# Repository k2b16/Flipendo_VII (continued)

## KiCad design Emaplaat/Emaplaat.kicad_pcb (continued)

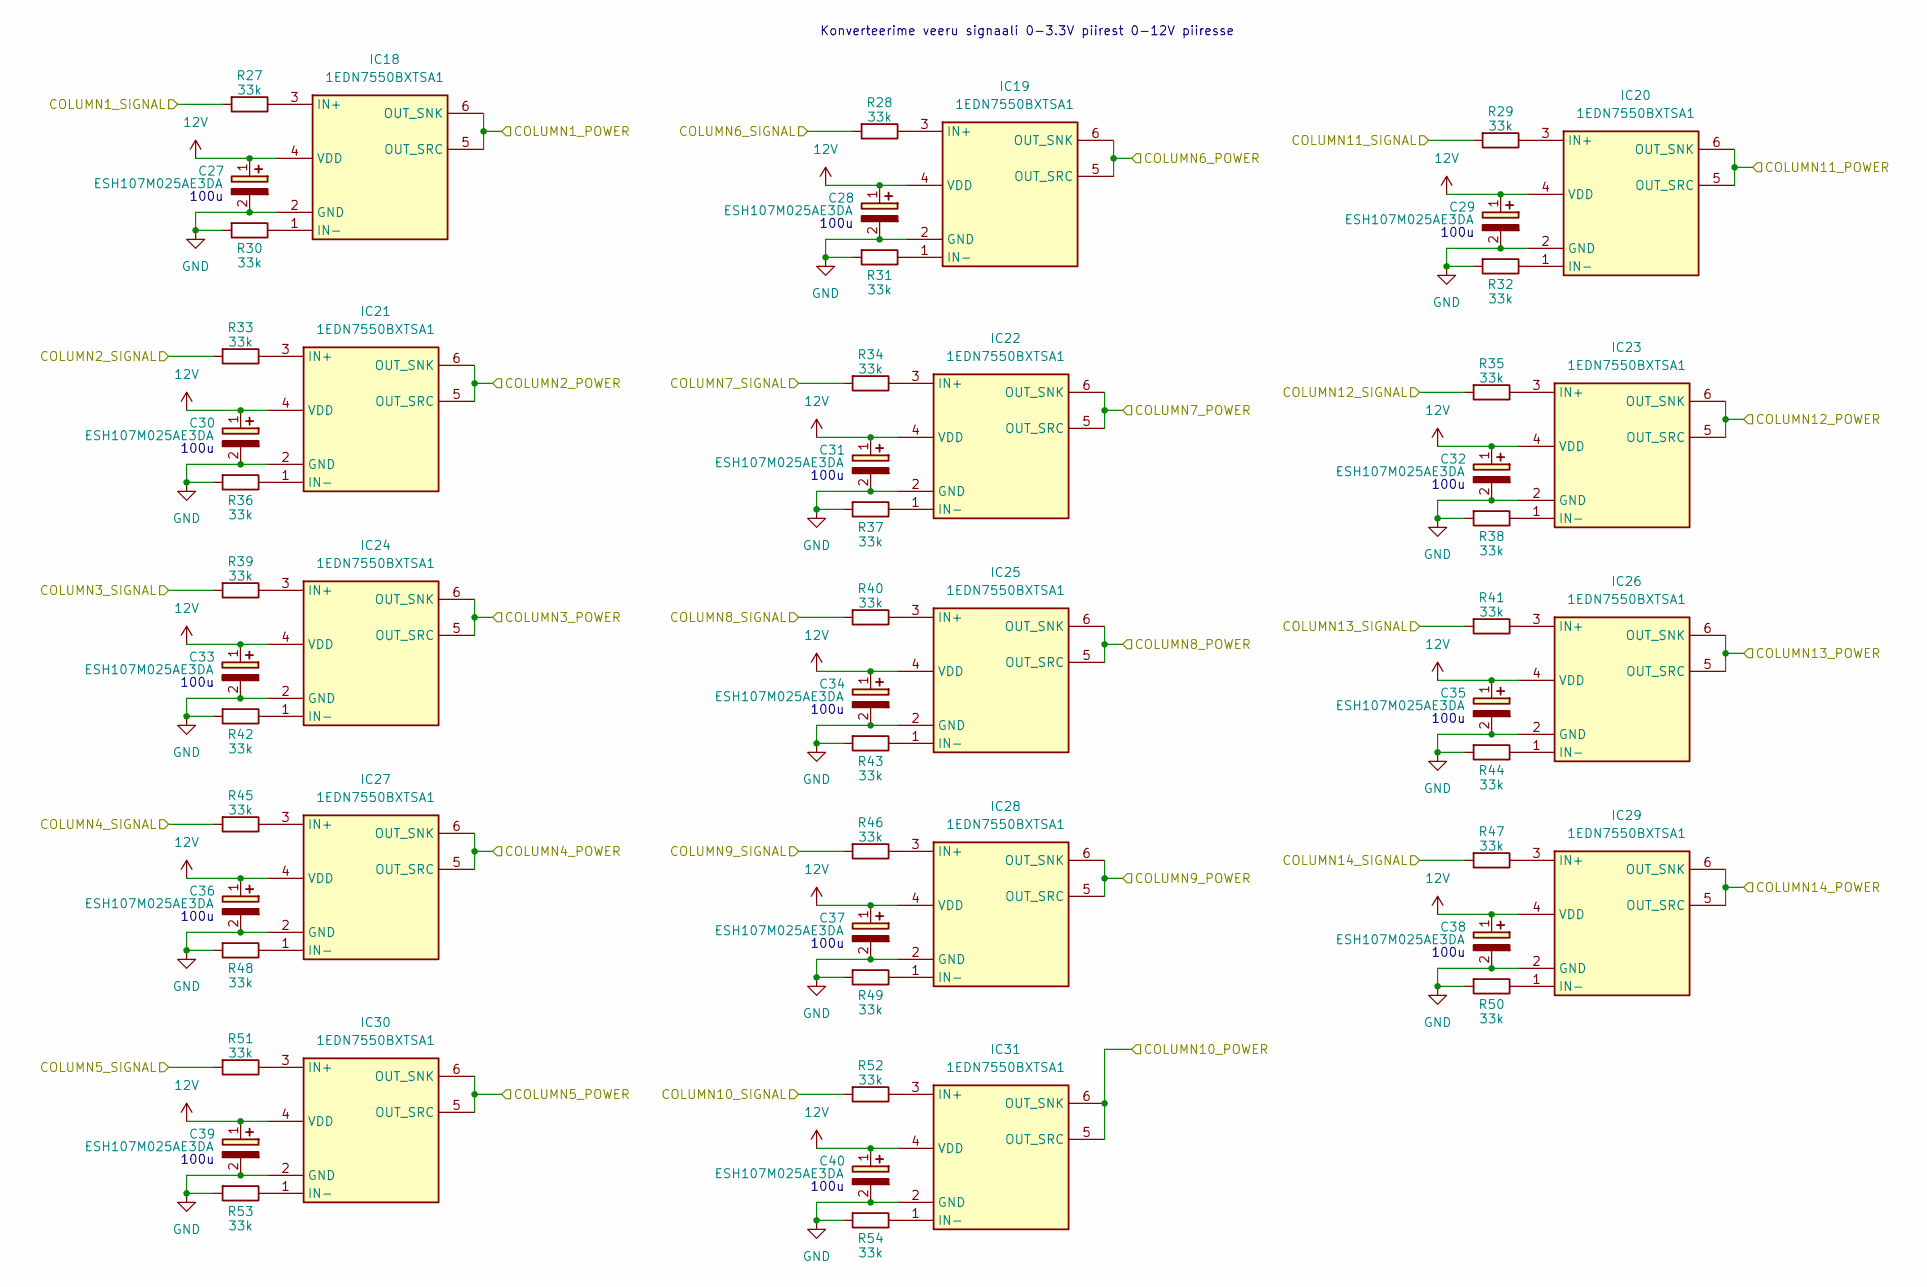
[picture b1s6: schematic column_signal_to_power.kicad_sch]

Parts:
C27, C28, C29, C30, C31, C32, C33, C34, C35, C36, C37, C38, C39, C40: ESH107M025AE3DA; CAPPRD250W50D630H1250; Mouser Part Number 80-ESH107M025AE3DA
IC18, IC19, IC20, IC21, IC22, IC23, IC24, IC25, IC26, IC27, IC28, IC29, IC30, IC31: 1EDN7550BXTSA1; SOT95P280X145-6N; Mouser Part Number 726-1EDN7550BXTSA1
R27, R28, R29, R30, R31, R32, R33, R34, R35, R36, R37, R38, R39, R40, R41, R42, R43, R44, R45, R46, R47, R48, R49, R50, R51, R52, R53, R54: 33k; R_0603_1608Metric_Pad0.98x0.95mm_HandSolder

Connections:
12V: C27.1 (+), C28.1 (+), C29.1 (+), C30.1 (+), C31.1 (+), C32.1 (+), C33.1 (+), C34.1 (+), C35.1 (+), C36.1 (+), C37.1 (+), C38.1 (+), C39.1 (+), C40.1 (+), IC18.4 (VDD), IC19.4 (VDD), IC20.4 (VDD), IC21.4 (VDD), IC22.4 (VDD), IC23.4 (VDD), IC24.4 (VDD), IC25.4 (VDD), IC26.4 (VDD), IC27.4 (VDD), IC28.4 (VDD), IC29.4 (VDD), IC30.4 (VDD), IC31.4 (VDD); also elsewhere on the board
/COLUMN1: R27.2; also elsewhere on the board
/COLUMN2: R33.2; also elsewhere on the board
/COLUMN3: R39.2; also elsewhere on the board
/COLUMN4: R45.2; also elsewhere on the board
/COLUMN5: R51.2; also elsewhere on the board
/COLUMN6: R28.2; also elsewhere on the board
/COLUMN7: R34.2; also elsewhere on the board
/COLUMN8: R40.2; also elsewhere on the board
/COLUMN9: R46.2; also elsewhere on the board
/COLUMN10: R52.2; also elsewhere on the board
/COLUMN11: R29.2; also elsewhere on the board
/COLUMN12: R35.2; also elsewhere on the board
/COLUMN13: R41.2; also elsewhere on the board
/COLUMN14: R47.2; also elsewhere on the board
/ekraan/COLUMN1_POWER: IC18.5 (OUT_SRC), IC18.6 (OUT_SNK); also elsewhere on the board
/ekraan/COLUMN2_POWER: IC21.5 (OUT_SRC), IC21.6 (OUT_SNK); also elsewhere on the board
/ekraan/COLUMN3_POWER: IC24.5 (OUT_SRC), IC24.6 (OUT_SNK); also elsewhere on the board
/ekraan/COLUMN4_POWER: IC27.5 (OUT_SRC), IC27.6 (OUT_SNK); also elsewhere on the board
/ekraan/COLUMN5_POWER: IC30.5 (OUT_SRC), IC30.6 (OUT_SNK); also elsewhere on the board
/ekraan/COLUMN6_POWER: IC19.5 (OUT_SRC), IC19.6 (OUT_SNK); also elsewhere on the board
/ekraan/COLUMN7_POWER: IC22.5 (OUT_SRC), IC22.6 (OUT_SNK); also elsewhere on the board
/ekraan/COLUMN8_POWER: IC25.5 (OUT_SRC), IC25.6 (OUT_SNK); also elsewhere on the board
/ekraan/COLUMN9_POWER: IC28.5 (OUT_SRC), IC28.6 (OUT_SNK); also elsewhere on the board
/ekraan/COLUMN10_POWER: IC31.5 (OUT_SRC), IC31.6 (OUT_SNK); also elsewhere on the board
/ekraan/COLUMN11_POWER: IC20.5 (OUT_SRC), IC20.6 (OUT_SNK); also elsewhere on the board
/ekraan/COLUMN12_POWER: IC23.5 (OUT_SRC), IC23.6 (OUT_SNK); also elsewhere on the board
/ekraan/COLUMN13_POWER: IC26.5 (OUT_SRC), IC26.6 (OUT_SNK); also elsewhere on the board
/ekraan/COLUMN14_POWER: IC29.5 (OUT_SRC), IC29.6 (OUT_SNK); also elsewhere on the board
GND: C27.2 (-), C28.2 (-), C29.2 (-), C30.2 (-), C31.2 (-), C32.2 (-), C33.2 (-), C34.2 (-), C35.2 (-), C36.2 (-), C37.2 (-), C38.2 (-), C39.2 (-), C40.2 (-), IC18.2 (GND), IC19.2 (GND), IC20.2 (GND), IC21.2 (GND), IC22.2 (GND), IC23.2 (GND), IC24.2 (GND), IC25.2 (GND), IC26.2 (GND), IC27.2 (GND), IC28.2 (GND), IC29.2 (GND), IC30.2 (GND), IC31.2 (GND), R30.2, R31.2, R32.2, R36.2, R37.2, R38.2, R42.2, R43.2, R44.2, R48.2, R49.2, R50.2, R53.2, R54.2; also elsewhere on the board
unnamed: IC18.3 (IN+), R27.1
unnamed: IC18.1 (IN-), R30.1
unnamed: IC19.3 (IN+), R28.1
unnamed: IC19.1 (IN-), R31.1
unnamed: IC20.3 (IN+), R29.1
unnamed: IC20.1 (IN-), R32.1
unnamed: IC21.3 (IN+), R33.1
unnamed: IC21.1 (IN-), R36.1
unnamed: IC22.3 (IN+), R34.1
unnamed: IC22.1 (IN-), R37.1
unnamed: IC23.3 (IN+), R35.1
unnamed: IC23.1 (IN-), R38.1
unnamed: IC24.3 (IN+), R39.1
unnamed: IC24.1 (IN-), R42.1
unnamed: IC25.3 (IN+), R40.1
unnamed: IC25.1 (IN-), R43.1
unnamed: IC26.3 (IN+), R41.1
unnamed: IC26.1 (IN-), R44.1
unnamed: IC27.3 (IN+), R45.1
unnamed: IC27.1 (IN-), R48.1
unnamed: IC28.3 (IN+), R46.1
unnamed: IC28.1 (IN-), R49.1
unnamed: IC29.3 (IN+), R47.1
unnamed: IC29.1 (IN-), R50.1
unnamed: IC30.3 (IN+), R51.1
unnamed: IC30.1 (IN-), R53.1
unnamed: IC31.3 (IN+), R52.1
unnamed: IC31.1 (IN-), R54.1

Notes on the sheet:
100u
Konverteerime veeru signaali 0-3.3V piirest 0-12V piiresse

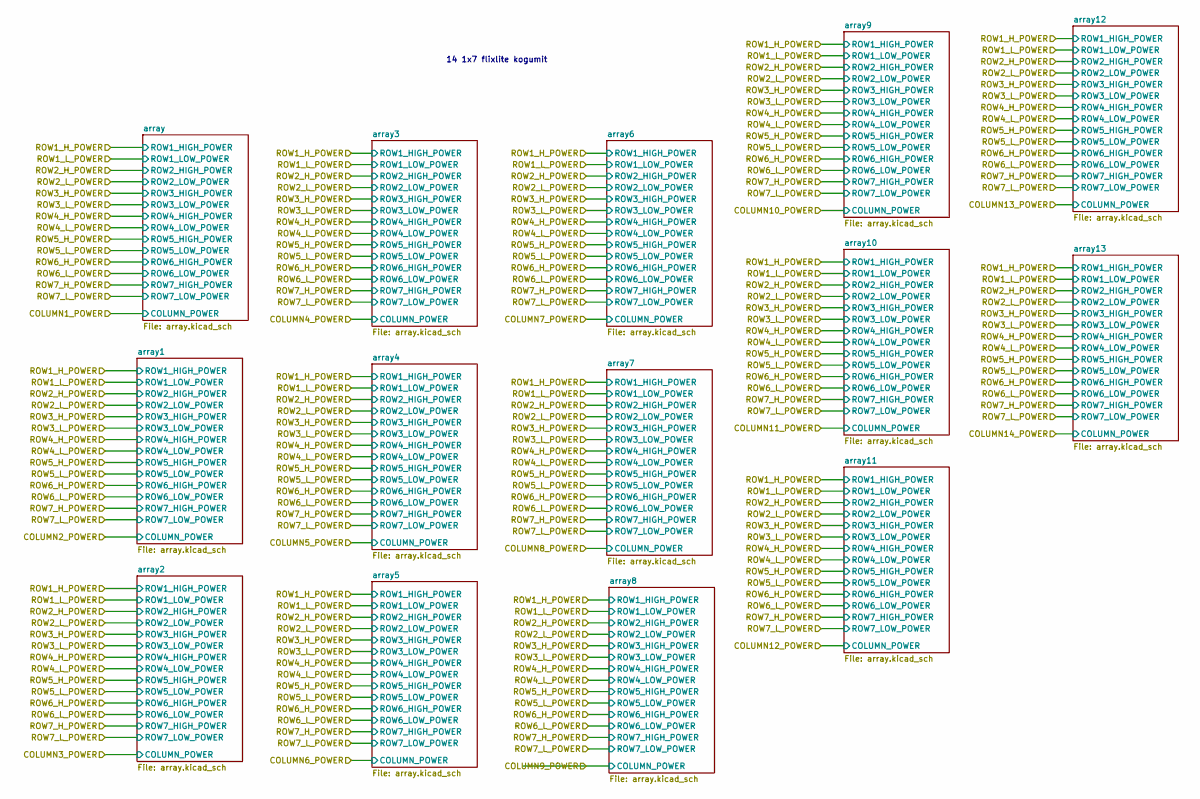
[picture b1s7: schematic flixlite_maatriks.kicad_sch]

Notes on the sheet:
14 1x7 flixlite kogumit

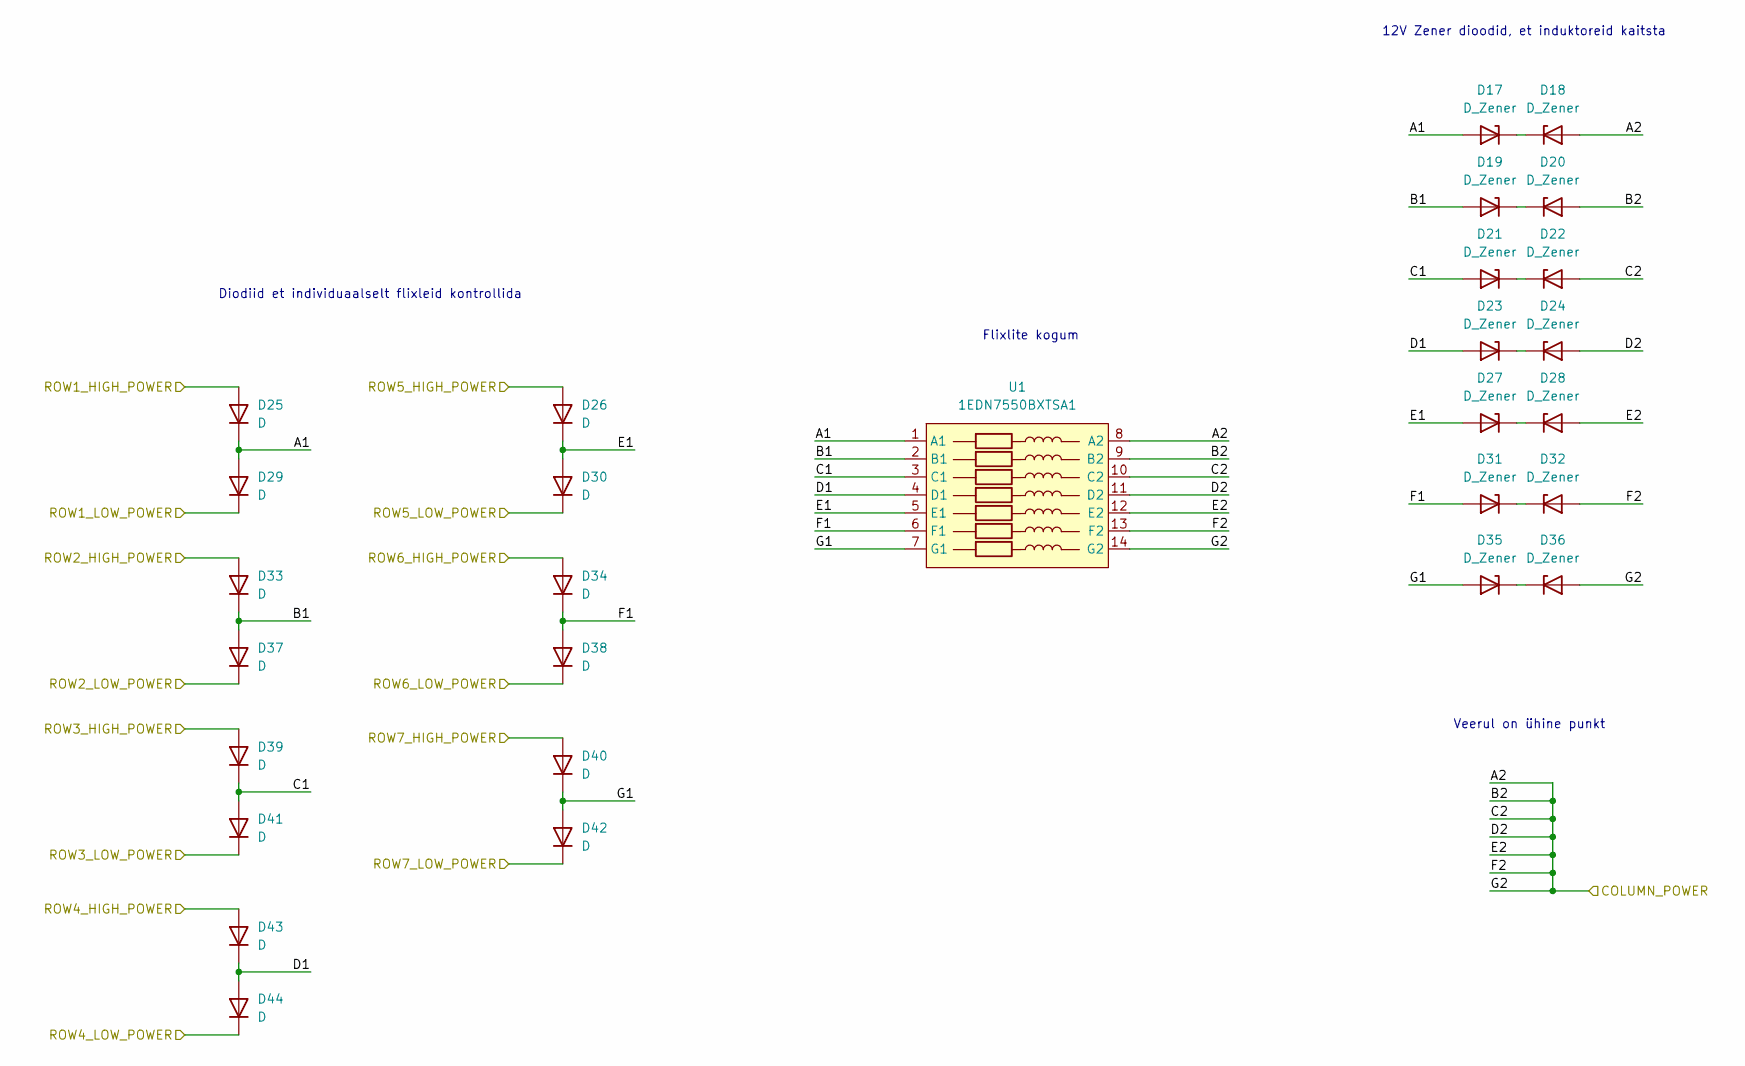
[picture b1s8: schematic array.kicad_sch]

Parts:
D17, D18, D19, D20, D21, D22, D23, D24, D27, D28, D31, D32, D35, D36: D_Zener; DO-214AC-2
D25, D26, D29, D30, D33, D34, D37, D38, D39, D40, D41, D42, D43, D44: D; SOD-123FL
U1: 1EDN7550BXTSA1; 7_flip_dots

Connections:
/ekraan/COLUMN1_POWER: D18.2 (A), D20.2 (A), D22.2 (A), D24.2 (A), D28.2 (A), D32.2 (A), D36.2 (A), U1.8 (A2), U1.9 (B2), U1.10 (C2), U1.11 (D2), U1.12 (E2), U1.13 (F2), U1.14 (G2); also elsewhere on the board
/ekraan/Flixlite_maatriks/array/A1: D17.2 (A), D25.1 (K), D29.2 (A), U1.1 (A1)
/ekraan/Flixlite_maatriks/array/B1: D19.2 (A), D33.1 (K), D37.2 (A), U1.2 (B1)
/ekraan/Flixlite_maatriks/array/C1: D21.2 (A), D39.1 (K), D41.2 (A), U1.3 (C1)
/ekraan/Flixlite_maatriks/array/D1: D23.2 (A), D43.1 (K), D44.2 (A), U1.4 (D1)
/ekraan/Flixlite_maatriks/array/E1: D26.1 (K), D27.2 (A), D30.2 (A), U1.5 (E1)
/ekraan/Flixlite_maatriks/array/F1: D31.2 (A), D34.1 (K), D38.2 (A), U1.6 (F1)
/ekraan/Flixlite_maatriks/array/G1: D35.2 (A), D40.1 (K), D42.2 (A), U1.7 (G1)
/ekraan/ROW1_H_POWER: D25.2 (A); also elsewhere on the board
/ekraan/ROW1_L_POWER: D29.1 (K); also elsewhere on the board
/ekraan/ROW2_H_POWER: D33.2 (A); also elsewhere on the board
/ekraan/ROW2_L_POWER: D37.1 (K); also elsewhere on the board
/ekraan/ROW3_H_POWER: D39.2 (A); also elsewhere on the board
/ekraan/ROW3_L_POWER: D41.1 (K); also elsewhere on the board
/ekraan/ROW4_H_POWER: D43.2 (A); also elsewhere on the board
/ekraan/ROW4_L_POWER: D44.1 (K); also elsewhere on the board
/ekraan/ROW5_H_POWER: D26.2 (A); also elsewhere on the board
/ekraan/ROW5_L_POWER: D30.1 (K); also elsewhere on the board
/ekraan/ROW6_H_POWER: D34.2 (A); also elsewhere on the board
/ekraan/ROW6_L_POWER: D38.1 (K); also elsewhere on the board
/ekraan/ROW7_H_POWER: D40.2 (A); also elsewhere on the board
/ekraan/ROW7_L_POWER: D42.1 (K); also elsewhere on the board
unnamed: D17.1 (K), D18.1 (K)
unnamed: D19.1 (K), D20.1 (K)
unnamed: D21.1 (K), D22.1 (K)
unnamed: D23.1 (K), D24.1 (K)
unnamed: D27.1 (K), D28.1 (K)
unnamed: D31.1 (K), D32.1 (K)
unnamed: D35.1 (K), D36.1 (K)

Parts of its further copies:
D45, D46, D47, D48, D49, D50, D51, D52, D55, D56, D59, D60, D63, D64, D73, D74, D75, D76, D77, D78, D79, D80, D83, D84, D87, D88, D91, D92, D101, D102, D103, D104, D105, D106, D107, D108, D111, D112, D115, D116, D119, D120, D129, D130, D131, D132, D133, D134, D135, D136, D139, D140, D143, D144, D147, D148, D157, D158, D159, D160, D161, D162, D163, D164, D167, D168, D171, D172, D175, D176, D185, D186, D187, D188, D189, D190, D191, D192, D195, D196, D199, D200, D203, D204, D213, D214, D215, D216, D217, D218, D219, D220, D223, D224, D227, D228, D231, D232, D241, D242, D243, D244, D245, D246, D247, D248, D251, D252, D255, D256, D259, D260, D269, D270, D271, D272, D273, D274, D275, D276, D279, D280, D283, D284, D287, D288, D297, D298, D299, D300, D301, D302, D303, D304, D307, D308, D311, D312, D315, D316, D325, D326, D327, D328, D329, D330, D331, D332, D335, D336, D339, D340, D343, D344, D353, D354, D355, D356, D357, D358, D359, D360, D363, D364, D367, D368, D371, D372, D381, D382, D383, D384, D385, D386, D387, D388, D391, D392, D395, D396, D399, D400: D_Zener; DO-214AC-2
D53, D54, D57, D58, D61, D62, D65, D66, D67, D68, D69, D70, D71, D72, D81, D82, D85, D86, D89, D90, D93, D94, D95, D96, D97, D98, D99, D100, D109, D110, D113, D114, D117, D118, D121, D122, D123, D124, D125, D126, D127, D128, D137, D138, D141, D142, D145, D146, D149, D150, D151, D152, D153, D154, D155, D156, D165, D166, D169, D170, D173, D174, D177, D178, D179, D180, D181, D182, D183, D184, D193, D194, D197, D198, D201, D202, D205, D206, D207, D208, D209, D210, D211, D212, D221, D222, D225, D226, D229, D230, D233, D234, D235, D236, D237, D238, D239, D240, D249, D250, D253, D254, D257, D258, D261, D262, D263, D264, D265, D266, D267, D268, D277, D278, D281, D282, D285, D286, D289, D290, D291, D292, D293, D294, D295, D296, D305, D306, D309, D310, D313, D314, D317, D318, D319, D320, D321, D322, D323, D324, D333, D334, D337, D338, D341, D342, D345, D346, D347, D348, D349, D350, D351, D352, D361, D362, D365, D366, D369, D370, D373, D374, D375, D376, D377, D378, D379, D380, D389, D390, D393, D394, D397, D398, D401, D402, D403, D404, D405, D406, D407, D408: D; SOD-123FL
U2, U3, U4, U5, U6, U7, U8, U9, U10, U11, U12, U13, U14: 1EDN7550BXTSA1; 7_flip_dots

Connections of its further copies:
/ekraan/COLUMN2_POWER: D46.2 (A), D48.2 (A), D50.2 (A), D52.2 (A), D56.2 (A), D60.2 (A), D64.2 (A), U2.8 (A2), U2.9 (B2), U2.10 (C2), U2.11 (D2), U2.12 (E2), U2.13 (F2), U2.14 (G2); also elsewhere on the board
/ekraan/COLUMN3_POWER: D74.2 (A), D76.2 (A), D78.2 (A), D80.2 (A), D84.2 (A), D88.2 (A), D92.2 (A), U3.8 (A2), U3.9 (B2), U3.10 (C2), U3.11 (D2), U3.12 (E2), U3.13 (F2), U3.14 (G2); also elsewhere on the board
/ekraan/COLUMN4_POWER: D102.2 (A), D104.2 (A), D106.2 (A), D108.2 (A), D112.2 (A), D116.2 (A), D120.2 (A), U4.8 (A2), U4.9 (B2), U4.10 (C2), U4.11 (D2), U4.12 (E2), U4.13 (F2), U4.14 (G2); also elsewhere on the board
/ekraan/COLUMN5_POWER: D130.2 (A), D132.2 (A), D134.2 (A), D136.2 (A), D140.2 (A), D144.2 (A), D148.2 (A), U5.8 (A2), U5.9 (B2), U5.10 (C2), U5.11 (D2), U5.12 (E2), U5.13 (F2), U5.14 (G2); also elsewhere on the board
/ekraan/COLUMN6_POWER: D158.2 (A), D160.2 (A), D162.2 (A), D164.2 (A), D168.2 (A), D172.2 (A), D176.2 (A), U6.8 (A2), U6.9 (B2), U6.10 (C2), U6.11 (D2), U6.12 (E2), U6.13 (F2), U6.14 (G2); also elsewhere on the board
/ekraan/COLUMN7_POWER: D186.2 (A), D188.2 (A), D190.2 (A), D192.2 (A), D196.2 (A), D200.2 (A), D204.2 (A), U7.8 (A2), U7.9 (B2), U7.10 (C2), U7.11 (D2), U7.12 (E2), U7.13 (F2), U7.14 (G2); also elsewhere on the board
/ekraan/COLUMN8_POWER: D214.2 (A), D216.2 (A), D218.2 (A), D220.2 (A), D224.2 (A), D228.2 (A), D232.2 (A), U8.8 (A2), U8.9 (B2), U8.10 (C2), U8.11 (D2), U8.12 (E2), U8.13 (F2), U8.14 (G2); also elsewhere on the board
/ekraan/COLUMN9_POWER: D242.2 (A), D244.2 (A), D246.2 (A), D248.2 (A), D252.2 (A), D256.2 (A), D260.2 (A), U9.8 (A2), U9.9 (B2), U9.10 (C2), U9.11 (D2), U9.12 (E2), U9.13 (F2), U9.14 (G2); also elsewhere on the board
/ekraan/COLUMN10_POWER: D270.2 (A), D272.2 (A), D274.2 (A), D276.2 (A), D280.2 (A), D284.2 (A), D288.2 (A), U10.8 (A2), U10.9 (B2), U10.10 (C2), U10.11 (D2), U10.12 (E2), U10.13 (F2), U10.14 (G2); also elsewhere on the board
/ekraan/COLUMN11_POWER: D298.2 (A), D300.2 (A), D302.2 (A), D304.2 (A), D308.2 (A), D312.2 (A), D316.2 (A), U11.8 (A2), U11.9 (B2), U11.10 (C2), U11.11 (D2), U11.12 (E2), U11.13 (F2), U11.14 (G2); also elsewhere on the board
/ekraan/COLUMN12_POWER: D326.2 (A), D328.2 (A), D330.2 (A), D332.2 (A), D336.2 (A), D340.2 (A), D344.2 (A), U12.8 (A2), U12.9 (B2), U12.10 (C2), U12.11 (D2), U12.12 (E2), U12.13 (F2), U12.14 (G2); also elsewhere on the board
/ekraan/COLUMN13_POWER: D354.2 (A), D356.2 (A), D358.2 (A), D360.2 (A), D364.2 (A), D368.2 (A), D372.2 (A), U13.8 (A2), U13.9 (B2), U13.10 (C2), U13.11 (D2), U13.12 (E2), U13.13 (F2), U13.14 (G2); also elsewhere on the board
/ekraan/COLUMN14_POWER: D382.2 (A), D384.2 (A), D386.2 (A), D388.2 (A), D392.2 (A), D396.2 (A), D400.2 (A), U14.8 (A2), U14.9 (B2), U14.10 (C2), U14.11 (D2), U14.12 (E2), U14.13 (F2), U14.14 (G2); also elsewhere on the board
/ekraan/Flixlite_maatriks/array1/A1: D45.2 (A), D53.1 (K), D57.2 (A), U2.1 (A1)
/ekraan/Flixlite_maatriks/array1/B1: D47.2 (A), D61.1 (K), D65.2 (A), U2.2 (B1)
/ekraan/Flixlite_maatriks/array1/C1: D49.2 (A), D67.1 (K), D69.2 (A), U2.3 (C1)
/ekraan/Flixlite_maatriks/array1/D1: D51.2 (A), D71.1 (K), D72.2 (A), U2.4 (D1)
/ekraan/Flixlite_maatriks/array1/E1: D54.1 (K), D55.2 (A), D58.2 (A), U2.5 (E1)
/ekraan/Flixlite_maatriks/array1/F1: D59.2 (A), D62.1 (K), D66.2 (A), U2.6 (F1)
/ekraan/Flixlite_maatriks/array1/G1: D63.2 (A), D68.1 (K), D70.2 (A), U2.7 (G1)
/ekraan/Flixlite_maatriks/array2/A1: D73.2 (A), D81.1 (K), D85.2 (A), U3.1 (A1)
/ekraan/Flixlite_maatriks/array2/B1: D75.2 (A), D89.1 (K), D93.2 (A), U3.2 (B1)
/ekraan/Flixlite_maatriks/array2/C1: D77.2 (A), D95.1 (K), D97.2 (A), U3.3 (C1)
/ekraan/Flixlite_maatriks/array2/D1: D79.2 (A), D99.1 (K), D100.2 (A), U3.4 (D1)
/ekraan/Flixlite_maatriks/array2/E1: D82.1 (K), D83.2 (A), D86.2 (A), U3.5 (E1)
/ekraan/Flixlite_maatriks/array2/F1: D87.2 (A), D90.1 (K), D94.2 (A), U3.6 (F1)
/ekraan/Flixlite_maatriks/array2/G1: D91.2 (A), D96.1 (K), D98.2 (A), U3.7 (G1)
/ekraan/Flixlite_maatriks/array3/A1: D101.2 (A), D109.1 (K), D113.2 (A), U4.1 (A1)
/ekraan/Flixlite_maatriks/array3/B1: D103.2 (A), D117.1 (K), D121.2 (A), U4.2 (B1)
/ekraan/Flixlite_maatriks/array3/C1: D105.2 (A), D123.1 (K), D125.2 (A), U4.3 (C1)
/ekraan/Flixlite_maatriks/array3/D1: D107.2 (A), D127.1 (K), D128.2 (A), U4.4 (D1)
/ekraan/Flixlite_maatriks/array3/E1: D110.1 (K), D111.2 (A), D114.2 (A), U4.5 (E1)
/ekraan/Flixlite_maatriks/array3/F1: D115.2 (A), D118.1 (K), D122.2 (A), U4.6 (F1)
/ekraan/Flixlite_maatriks/array3/G1: D119.2 (A), D124.1 (K), D126.2 (A), U4.7 (G1)
/ekraan/Flixlite_maatriks/array4/A1: D129.2 (A), D137.1 (K), D141.2 (A), U5.1 (A1)
/ekraan/Flixlite_maatriks/array4/B1: D131.2 (A), D145.1 (K), D149.2 (A), U5.2 (B1)
/ekraan/Flixlite_maatriks/array4/C1: D133.2 (A), D151.1 (K), D153.2 (A), U5.3 (C1)
/ekraan/Flixlite_maatriks/array4/D1: D135.2 (A), D155.1 (K), D156.2 (A), U5.4 (D1)
/ekraan/Flixlite_maatriks/array4/E1: D138.1 (K), D139.2 (A), D142.2 (A), U5.5 (E1)
/ekraan/Flixlite_maatriks/array4/F1: D143.2 (A), D146.1 (K), D150.2 (A), U5.6 (F1)
/ekraan/Flixlite_maatriks/array4/G1: D147.2 (A), D152.1 (K), D154.2 (A), U5.7 (G1)
/ekraan/Flixlite_maatriks/array5/A1: D157.2 (A), D165.1 (K), D169.2 (A), U6.1 (A1)
/ekraan/Flixlite_maatriks/array5/B1: D159.2 (A), D173.1 (K), D177.2 (A), U6.2 (B1)
/ekraan/Flixlite_maatriks/array5/C1: D161.2 (A), D179.1 (K), D181.2 (A), U6.3 (C1)
/ekraan/Flixlite_maatriks/array5/D1: D163.2 (A), D183.1 (K), D184.2 (A), U6.4 (D1)
/ekraan/Flixlite_maatriks/array5/E1: D166.1 (K), D167.2 (A), D170.2 (A), U6.5 (E1)
/ekraan/Flixlite_maatriks/array5/F1: D171.2 (A), D174.1 (K), D178.2 (A), U6.6 (F1)
/ekraan/Flixlite_maatriks/array5/G1: D175.2 (A), D180.1 (K), D182.2 (A), U6.7 (G1)
/ekraan/Flixlite_maatriks/array6/A1: D185.2 (A), D193.1 (K), D197.2 (A), U7.1 (A1)
/ekraan/Flixlite_maatriks/array6/B1: D187.2 (A), D201.1 (K), D205.2 (A), U7.2 (B1)
/ekraan/Flixlite_maatriks/array6/C1: D189.2 (A), D207.1 (K), D209.2 (A), U7.3 (C1)
/ekraan/Flixlite_maatriks/array6/D1: D191.2 (A), D211.1 (K), D212.2 (A), U7.4 (D1)
/ekraan/Flixlite_maatriks/array6/E1: D194.1 (K), D195.2 (A), D198.2 (A), U7.5 (E1)
/ekraan/Flixlite_maatriks/array6/F1: D199.2 (A), D202.1 (K), D206.2 (A), U7.6 (F1)
/ekraan/Flixlite_maatriks/array6/G1: D203.2 (A), D208.1 (K), D210.2 (A), U7.7 (G1)
/ekraan/Flixlite_maatriks/array7/A1: D213.2 (A), D221.1 (K), D225.2 (A), U8.1 (A1)
/ekraan/Flixlite_maatriks/array7/B1: D215.2 (A), D229.1 (K), D233.2 (A), U8.2 (B1)
/ekraan/Flixlite_maatriks/array7/C1: D217.2 (A), D235.1 (K), D237.2 (A), U8.3 (C1)
/ekraan/Flixlite_maatriks/array7/D1: D219.2 (A), D239.1 (K), D240.2 (A), U8.4 (D1)
/ekraan/Flixlite_maatriks/array7/E1: D222.1 (K), D223.2 (A), D226.2 (A), U8.5 (E1)
/ekraan/Flixlite_maatriks/array7/F1: D227.2 (A), D230.1 (K), D234.2 (A), U8.6 (F1)
/ekraan/Flixlite_maatriks/array7/G1: D231.2 (A), D236.1 (K), D238.2 (A), U8.7 (G1)
/ekraan/Flixlite_maatriks/array8/A1: D241.2 (A), D249.1 (K), D253.2 (A), U9.1 (A1)
/ekraan/Flixlite_maatriks/array8/B1: D243.2 (A), D257.1 (K), D261.2 (A), U9.2 (B1)
/ekraan/Flixlite_maatriks/array8/C1: D245.2 (A), D263.1 (K), D265.2 (A), U9.3 (C1)
/ekraan/Flixlite_maatriks/array8/D1: D247.2 (A), D267.1 (K), D268.2 (A), U9.4 (D1)
/ekraan/Flixlite_maatriks/array8/E1: D250.1 (K), D251.2 (A), D254.2 (A), U9.5 (E1)
/ekraan/Flixlite_maatriks/array8/F1: D255.2 (A), D258.1 (K), D262.2 (A), U9.6 (F1)
/ekraan/Flixlite_maatriks/array8/G1: D259.2 (A), D264.1 (K), D266.2 (A), U9.7 (G1)
/ekraan/Flixlite_maatriks/array9/A1: D269.2 (A), D277.1 (K), D281.2 (A), U10.1 (A1)
/ekraan/Flixlite_maatriks/array9/B1: D271.2 (A), D285.1 (K), D289.2 (A), U10.2 (B1)
/ekraan/Flixlite_maatriks/array9/C1: D273.2 (A), D291.1 (K), D293.2 (A), U10.3 (C1)
/ekraan/Flixlite_maatriks/array9/D1: D275.2 (A), D295.1 (K), D296.2 (A), U10.4 (D1)
/ekraan/Flixlite_maatriks/array9/E1: D278.1 (K), D279.2 (A), D282.2 (A), U10.5 (E1)
/ekraan/Flixlite_maatriks/array9/F1: D283.2 (A), D286.1 (K), D290.2 (A), U10.6 (F1)
/ekraan/Flixlite_maatriks/array9/G1: D287.2 (A), D292.1 (K), D294.2 (A), U10.7 (G1)
/ekraan/Flixlite_maatriks/array10/A1: D297.2 (A), D305.1 (K), D309.2 (A), U11.1 (A1)
/ekraan/Flixlite_maatriks/array10/B1: D299.2 (A), D313.1 (K), D317.2 (A), U11.2 (B1)
/ekraan/Flixlite_maatriks/array10/C1: D301.2 (A), D319.1 (K), D321.2 (A), U11.3 (C1)
/ekraan/Flixlite_maatriks/array10/D1: D303.2 (A), D323.1 (K), D324.2 (A), U11.4 (D1)
/ekraan/Flixlite_maatriks/array10/E1: D306.1 (K), D307.2 (A), D310.2 (A), U11.5 (E1)
/ekraan/Flixlite_maatriks/array10/F1: D311.2 (A), D314.1 (K), D318.2 (A), U11.6 (F1)
/ekraan/Flixlite_maatriks/array10/G1: D315.2 (A), D320.1 (K), D322.2 (A), U11.7 (G1)
/ekraan/Flixlite_maatriks/array11/A1: D325.2 (A), D333.1 (K), D337.2 (A), U12.1 (A1)
/ekraan/Flixlite_maatriks/array11/B1: D327.2 (A), D341.1 (K), D345.2 (A), U12.2 (B1)
/ekraan/Flixlite_maatriks/array11/C1: D329.2 (A), D347.1 (K), D349.2 (A), U12.3 (C1)
/ekraan/Flixlite_maatriks/array11/D1: D331.2 (A), D351.1 (K), D352.2 (A), U12.4 (D1)
/ekraan/Flixlite_maatriks/array11/E1: D334.1 (K), D335.2 (A), D338.2 (A), U12.5 (E1)
/ekraan/Flixlite_maatriks/array11/F1: D339.2 (A), D342.1 (K), D346.2 (A), U12.6 (F1)
/ekraan/Flixlite_maatriks/array11/G1: D343.2 (A), D348.1 (K), D350.2 (A), U12.7 (G1)
/ekraan/Flixlite_maatriks/array12/A1: D353.2 (A), D361.1 (K), D365.2 (A), U13.1 (A1)
/ekraan/Flixlite_maatriks/array12/B1: D355.2 (A), D369.1 (K), D373.2 (A), U13.2 (B1)
/ekraan/Flixlite_maatriks/array12/C1: D357.2 (A), D375.1 (K), D377.2 (A), U13.3 (C1)
/ekraan/Flixlite_maatriks/array12/D1: D359.2 (A), D379.1 (K), D380.2 (A), U13.4 (D1)
/ekraan/Flixlite_maatriks/array12/E1: D362.1 (K), D363.2 (A), D366.2 (A), U13.5 (E1)
/ekraan/Flixlite_maatriks/array12/F1: D367.2 (A), D370.1 (K), D374.2 (A), U13.6 (F1)
/ekraan/Flixlite_maatriks/array12/G1: D371.2 (A), D376.1 (K), D378.2 (A), U13.7 (G1)
/ekraan/Flixlite_maatriks/array13/A1: D381.2 (A), D389.1 (K), D393.2 (A), U14.1 (A1)
/ekraan/Flixlite_maatriks/array13/B1: D383.2 (A), D397.1 (K), D401.2 (A), U14.2 (B1)
/ekraan/Flixlite_maatriks/array13/C1: D385.2 (A), D403.1 (K), D405.2 (A), U14.3 (C1)
/ekraan/Flixlite_maatriks/array13/D1: D387.2 (A), D407.1 (K), D408.2 (A), U14.4 (D1)
/ekraan/Flixlite_maatriks/array13/E1: D390.1 (K), D391.2 (A), D394.2 (A), U14.5 (E1)
/ekraan/Flixlite_maatriks/array13/F1: D395.2 (A), D398.1 (K), D402.2 (A), U14.6 (F1)
/ekraan/Flixlite_maatriks/array13/G1: D399.2 (A), D404.1 (K), D406.2 (A), U14.7 (G1)
/ekraan/ROW1_H_POWER: D53.2 (A), D81.2 (A), D109.2 (A), D137.2 (A), D165.2 (A), D193.2 (A), D221.2 (A), D249.2 (A), D277.2 (A), D305.2 (A), D333.2 (A), D361.2 (A), D389.2 (A); also elsewhere on the board
/ekraan/ROW1_L_POWER: D57.1 (K), D85.1 (K), D113.1 (K), D141.1 (K), D169.1 (K), D197.1 (K), D225.1 (K), D253.1 (K), D281.1 (K), D309.1 (K), D337.1 (K), D365.1 (K), D393.1 (K); also elsewhere on the board
/ekraan/ROW2_H_POWER: D61.2 (A), D89.2 (A), D117.2 (A), D145.2 (A), D173.2 (A), D201.2 (A), D229.2 (A), D257.2 (A), D285.2 (A), D313.2 (A), D341.2 (A), D369.2 (A), D397.2 (A); also elsewhere on the board
/ekraan/ROW2_L_POWER: D65.1 (K), D93.1 (K), D121.1 (K), D149.1 (K), D177.1 (K), D205.1 (K), D233.1 (K), D261.1 (K), D289.1 (K), D317.1 (K), D345.1 (K), D373.1 (K), D401.1 (K); also elsewhere on the board
/ekraan/ROW3_H_POWER: D67.2 (A), D95.2 (A), D123.2 (A), D151.2 (A), D179.2 (A), D207.2 (A), D235.2 (A), D263.2 (A), D291.2 (A), D319.2 (A), D347.2 (A), D375.2 (A), D403.2 (A); also elsewhere on the board
/ekraan/ROW3_L_POWER: D69.1 (K), D97.1 (K), D125.1 (K), D153.1 (K), D181.1 (K), D209.1 (K), D237.1 (K), D265.1 (K), D293.1 (K), D321.1 (K), D349.1 (K), D377.1 (K), D405.1 (K); also elsewhere on the board
/ekraan/ROW4_H_POWER: D71.2 (A), D99.2 (A), D127.2 (A), D155.2 (A), D183.2 (A), D211.2 (A), D239.2 (A), D267.2 (A), D295.2 (A), D323.2 (A), D351.2 (A), D379.2 (A), D407.2 (A); also elsewhere on the board
/ekraan/ROW4_L_POWER: D72.1 (K), D100.1 (K), D128.1 (K), D156.1 (K), D184.1 (K), D212.1 (K), D240.1 (K), D268.1 (K), D296.1 (K), D324.1 (K), D352.1 (K), D380.1 (K), D408.1 (K); also elsewhere on the board
/ekraan/ROW5_H_POWER: D54.2 (A), D82.2 (A), D110.2 (A), D138.2 (A), D166.2 (A), D194.2 (A), D222.2 (A), D250.2 (A), D278.2 (A), D306.2 (A), D334.2 (A), D362.2 (A), D390.2 (A); also elsewhere on the board
/ekraan/ROW5_L_POWER: D58.1 (K), D86.1 (K), D114.1 (K), D142.1 (K), D170.1 (K), D198.1 (K), D226.1 (K), D254.1 (K), D282.1 (K), D310.1 (K), D338.1 (K), D366.1 (K), D394.1 (K); also elsewhere on the board
/ekraan/ROW6_H_POWER: D62.2 (A), D90.2 (A), D118.2 (A), D146.2 (A), D174.2 (A), D202.2 (A), D230.2 (A), D258.2 (A), D286.2 (A), D314.2 (A), D342.2 (A), D370.2 (A), D398.2 (A); also elsewhere on the board
/ekraan/ROW6_L_POWER: D66.1 (K), D94.1 (K), D122.1 (K), D150.1 (K), D178.1 (K), D206.1 (K), D234.1 (K), D262.1 (K), D290.1 (K), D318.1 (K), D346.1 (K), D374.1 (K), D402.1 (K); also elsewhere on the board
/ekraan/ROW7_H_POWER: D68.2 (A), D96.2 (A), D124.2 (A), D152.2 (A), D180.2 (A), D208.2 (A), D236.2 (A), D264.2 (A), D292.2 (A), D320.2 (A), D348.2 (A), D376.2 (A), D404.2 (A); also elsewhere on the board
/ekraan/ROW7_L_POWER: D70.1 (K), D98.1 (K), D126.1 (K), D154.1 (K), D182.1 (K), D210.1 (K), D238.1 (K), D266.1 (K), D294.1 (K), D322.1 (K), D350.1 (K), D378.1 (K), D406.1 (K); also elsewhere on the board
unnamed: D45.1 (K), D46.1 (K)
unnamed: D47.1 (K), D48.1 (K)
unnamed: D49.1 (K), D50.1 (K)
unnamed: D51.1 (K), D52.1 (K)
unnamed: D55.1 (K), D56.1 (K)
unnamed: D59.1 (K), D60.1 (K)
unnamed: D63.1 (K), D64.1 (K)
unnamed: D73.1 (K), D74.1 (K)
unnamed: D75.1 (K), D76.1 (K)
unnamed: D77.1 (K), D78.1 (K)
unnamed: D79.1 (K), D80.1 (K)
unnamed: D83.1 (K), D84.1 (K)
unnamed: D87.1 (K), D88.1 (K)
unnamed: D91.1 (K), D92.1 (K)
unnamed: D101.1 (K), D102.1 (K)
unnamed: D103.1 (K), D104.1 (K)
unnamed: D105.1 (K), D106.1 (K)
unnamed: D107.1 (K), D108.1 (K)
unnamed: D111.1 (K), D112.1 (K)
unnamed: D115.1 (K), D116.1 (K)
unnamed: D119.1 (K), D120.1 (K)
unnamed: D129.1 (K), D130.1 (K)
unnamed: D131.1 (K), D132.1 (K)
unnamed: D133.1 (K), D134.1 (K)
unnamed: D135.1 (K), D136.1 (K)
unnamed: D139.1 (K), D140.1 (K)
unnamed: D143.1 (K), D144.1 (K)
unnamed: D147.1 (K), D148.1 (K)
unnamed: D157.1 (K), D158.1 (K)
unnamed: D159.1 (K), D160.1 (K)
unnamed: D161.1 (K), D162.1 (K)
unnamed: D163.1 (K), D164.1 (K)
unnamed: D167.1 (K), D168.1 (K)
unnamed: D171.1 (K), D172.1 (K)
unnamed: D175.1 (K), D176.1 (K)
unnamed: D185.1 (K), D186.1 (K)
unnamed: D187.1 (K), D188.1 (K)
unnamed: D189.1 (K), D190.1 (K)
unnamed: D191.1 (K), D192.1 (K)
unnamed: D195.1 (K), D196.1 (K)
unnamed: D199.1 (K), D200.1 (K)
unnamed: D203.1 (K), D204.1 (K)
unnamed: D213.1 (K), D214.1 (K)
unnamed: D215.1 (K), D216.1 (K)
unnamed: D217.1 (K), D218.1 (K)
unnamed: D219.1 (K), D220.1 (K)
unnamed: D223.1 (K), D224.1 (K)
unnamed: D227.1 (K), D228.1 (K)
unnamed: D231.1 (K), D232.1 (K)
unnamed: D241.1 (K), D242.1 (K)
unnamed: D243.1 (K), D244.1 (K)
unnamed: D245.1 (K), D246.1 (K)
unnamed: D247.1 (K), D248.1 (K)
unnamed: D251.1 (K), D252.1 (K)
unnamed: D255.1 (K), D256.1 (K)
unnamed: D259.1 (K), D260.1 (K)
unnamed: D269.1 (K), D270.1 (K)
unnamed: D271.1 (K), D272.1 (K)
unnamed: D273.1 (K), D274.1 (K)
unnamed: D275.1 (K), D276.1 (K)
unnamed: D279.1 (K), D280.1 (K)
unnamed: D283.1 (K), D284.1 (K)
unnamed: D287.1 (K), D288.1 (K)
unnamed: D297.1 (K), D298.1 (K)
unnamed: D299.1 (K), D300.1 (K)
unnamed: D301.1 (K), D302.1 (K)
unnamed: D303.1 (K), D304.1 (K)
unnamed: D307.1 (K), D308.1 (K)
unnamed: D311.1 (K), D312.1 (K)
unnamed: D315.1 (K), D316.1 (K)
unnamed: D325.1 (K), D326.1 (K)
unnamed: D327.1 (K), D328.1 (K)
unnamed: D329.1 (K), D330.1 (K)
unnamed: D331.1 (K), D332.1 (K)
unnamed: D335.1 (K), D336.1 (K)
unnamed: D339.1 (K), D340.1 (K)
unnamed: D343.1 (K), D344.1 (K)
unnamed: D353.1 (K), D354.1 (K)
unnamed: D355.1 (K), D356.1 (K)
unnamed: D357.1 (K), D358.1 (K)
unnamed: D359.1 (K), D360.1 (K)
unnamed: D363.1 (K), D364.1 (K)
unnamed: D367.1 (K), D368.1 (K)
unnamed: D371.1 (K), D372.1 (K)
unnamed: D381.1 (K), D382.1 (K)
unnamed: D383.1 (K), D384.1 (K)
unnamed: D385.1 (K), D386.1 (K)
unnamed: D387.1 (K), D388.1 (K)
unnamed: D391.1 (K), D392.1 (K)
unnamed: D395.1 (K), D396.1 (K)
unnamed: D399.1 (K), D400.1 (K)

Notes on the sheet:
Flixlite kogum
Veerul on ühine punkt
Diodiid et individuaalselt flixleid kontrollida
12V Zener dioodid, et induktoreid kaitsta
